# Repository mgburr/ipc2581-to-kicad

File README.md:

# IPC-2581 / ODB++ to KiCad Converter

A command-line utility and GUI application that converts IPC-2581 XML and ODB++ files to KiCad `.kicad_pcb` format.

## Features

- Converts **IPC-2581** revision B/C XML files to KiCad PCB format
- Converts **ODB++** archives (.tgz, .zip) and extracted directories to KiCad PCB format
- Supports **KiCad 7.x**, **8.x**, and **9.x** output formats
- Parses complete PCB data:
  - Board outline (with arcs/curves)
  - Layer stackup with materials and dielectric properties
  - Component footprints and placements
  - Copper traces and arcs
  - Vias (through-hole and blind/buried)
  - Copper pours/zones
  - Pad stacks (SMD, through-hole, NPTH)
  - Net connectivity
  - Silkscreen, soldermask, paste layers
- JSON import/export for interoperability
- GUI application for easy point-and-click conversion
- Cross-platform (macOS, Linux, Windows)

## Building

### Requirements

- CMake 3.14+
- C++17 compiler (GCC, Clang, MSVC)
- Python 3.x (required for ODB++ support and GUI)

### Build Steps

```bash
mkdir build && cd build
cmake ..
make
```

The executable `ipc2581-to-kicad` will be created in the `build/` directory.

## Usage

### Command Line

```
Usage: ipc2581-to-kicad [options] <input>

Supported input formats:
  .xml, .cvg          IPC-2581 XML files
  .tgz, .tar.gz, .zip ODB++ archives (requires Python 3)
  directory/           ODB++ extracted directory (requires Python 3)
  .json                JSON (with --import-json)

Options:
  -o, --output <file>       Output .kicad_pcb file (default: <input>.kicad_pcb)
  -v, --version <7|8|9>     Target KiCad version (default: 9)
  -s, --step <name>         Step name to convert (default: first step)
  --list-steps              List available steps and exit
  --list-layers             List layer mapping and exit
  --export-json             Export parsed PCB data as JSON to stdout
  --import-json             Import from JSON file (output of --export-json)
  --verbose                 Verbose output during conversion
  -h, --help                Show help
```

### Examples

```bash
# Convert IPC-2581 XML (auto-detected by .xml extension)
./build/ipc2581-to-kicad board.xml

# Convert ODB++ archive (auto-detected by .tgz extension)
./build/ipc2581-to-kicad board.tgz -o output.kicad_pcb

# Convert ODB++ directory
./build/ipc2581-to-kicad /path/to/odb_directory/ -o output.kicad_pcb

# Specify KiCad version
./build/ipc2581-to-kicad -v 8 board.tgz -o output.kicad_pcb

# List available steps
./build/ipc2581-to-kicad --list-steps board.tgz

# Convert a specific step with verbose output
./build/ipc2581-to-kicad -s "MainBoard" --verbose board.xml

# Export to JSON, then re-import
./build/ipc2581-to-kicad --export-json board.xml > board.json
./build/ipc2581-to-kicad --import-json board.json -o board.kicad_pcb

# Show layer mapping
./build/ipc2581-to-kicad --list-layers board.xml
```

### ODB++ Python Parser (standalone)

The ODB++ parser can also be used directly:

```bash
# Output JSON to stdout
python3 odb/odb_to_json.py board.tgz

# List steps in an ODB++ archive
python3 odb/odb_to_json.py --list-steps board.tgz

# Verbose mode
python3 odb/odb_to_json.py -v board.tgz > board.json
```

### GUI Application

A graphical interface is available in the `gui/` folder:

```bash
# macOS/Linux
./gui/run_gui.sh

# Windows
gui\run_gui.bat

# macOS (double-click)
# Open gui/IPC2581-Converter.command in Finder
```

The GUI provides:
- File browser supporting both IPC-2581 (.xml, .cvg) and ODB++ (.tgz, .zip) files
- KiCad version selection (7, 8, or 9)
- Step selection dropdown
- Layer mapping preview
- 2D and 3D board viewers
- Progress indication and log output

## Architecture

```
IPC-2581 (.xml/.cvg)
  -> [C++: ipc2581_parser.cpp]
  -> PcbModel
  -> [C++: kicad_writer.cpp]
  -> .kicad_pcb

ODB++ (.tgz/.zip/dir)
  -> [Python: odb/odb_to_json.py]
  -> JSON (stdout)
  -> [C++: json_import.cpp]
  -> PcbModel
  -> [C++: kicad_writer.cpp]
  -> .kicad_pcb
```

Both paths share the same C++ `PcbModel` and `KicadWriter`, ensuring consistent output.

## Sample Files

A sample IPC-2581 file is provided in `samples/`:

```bash
./build/ipc2581-to-kicad samples/led_power_board.xml -o samples/led_power_board.kicad_pcb
```

Open the output in KiCad to see:
- 40x25mm board with rounded corner
- Voltage regulator circuit with LED
- SMD and through-hole components
- Top and bottom copper layers
- Ground plane (zone fill)
- Multiple net classes

## Layer Mapping

### IPC-2581

| IPC-2581 layerFunction | KiCad Layer |
|------------------------|-------------|
| SIGNAL, POWER_GROUND (top) | F.Cu |
| SIGNAL, POWER_GROUND (bottom) | B.Cu |
| SIGNAL, POWER_GROUND (inner) | In{N}.Cu |
| SOLDERMASK (top/bottom) | F.Mask / B.Mask |
| PASTEMASK (top/bottom) | F.Paste / B.Paste |
| SILKSCREEN (top/bottom) | F.SilkS / B.SilkS |
| ASSEMBLY (top/bottom) | F.Fab / B.Fab |
| BOARD_OUTLINE | Edge.Cuts |
| DOCUMENT | Cmts.User |

### ODB++

| ODB++ Layer Type | KiCad Layer |
|------------------|-------------|
| SIGNAL (first copper) | F.Cu |
| SIGNAL (last copper) | B.Cu |
| SIGNAL (inner copper) | In{N}.Cu |
| SOLDER_MASK | F.Mask / B.Mask |
| SILK_SCREEN | F.SilkS / B.SilkS |
| SOLDER_PASTE | F.Paste / B.Paste |
| COMPONENT | F.Fab / B.Fab |
| DRILL | (vias/holes) |

## Project Structure

```
ipc2581-to-kicad/
├── CMakeLists.txt          # Build configuration
├── README.md
├── src/
│   ├── main.cpp            # CLI entry point (IPC-2581 + ODB++ + JSON)
│   ├── pcb_model.h         # Intermediate data model
│   ├── geometry.h/.cpp     # Geometry primitives
│   ├── utils.h/.cpp        # Utility functions
│   ├── ipc2581_parser.h/.cpp  # IPC-2581 XML parser
│   ├── json_export.h/.cpp  # PcbModel -> JSON serialization
│   ├── json_import.h/.cpp  # JSON -> PcbModel deserialization
│   └── kicad_writer.h/.cpp # KiCad output writer
├── odb/
│   ├── __init__.py         # Python package
│   ├── pcb_model.py        # Python PCB data model
│   ├── odb_parser.py       # ODB++ format parser
│   ├── utils.py            # Utility functions
│   └── odb_to_json.py      # ODB++ -> JSON bridge
├── third_party/
│   ├── pugixml/            # XML parser (vendored)
│   └── nlohmann/           # JSON parser (vendored, single-header)
├── gui/
│   ├── ipc2581_gui.py      # Python/tkinter GUI
│   ├── pcb_data.py         # PCB data layer (supports IPC-2581 + ODB++)
│   ├── run_gui.sh          # Linux/macOS launcher
│   ├── run_gui.bat         # Windows launcher
│   └── IPC2581-Converter.command  # macOS double-click launcher
├── test/
│   └── test_odb.py         # ODB++ parser and JSON bridge tests
└── samples/
    └── led_power_board.xml # Sample IPC-2581 file
```

## Testing

```bash
# Run ODB++ unit tests
python3 -m pytest test/test_odb.py -v
```

## Technical Notes

### Coordinate System
Both IPC-2581 and ODB++ use Y+ up, while KiCad uses Y+ down. The converter automatically flips Y coordinates.

### Arc Conversion
IPC-2581 uses center+sweep angle arcs; ODB++ uses center+CW/CCW arcs; KiCad uses start/mid/end points. Both parsers handle these transformations.

### UUID Generation
KiCad 8/9 requires UUIDs on all elements. The converter generates deterministic UUIDs based on object properties to ensure reproducible output.

### JSON Schema
The JSON interchange format is documented in the source. Use `--export-json` to see the schema for any input file. The same schema is produced by both the C++ IPC-2581 parser and the Python ODB++ parser.

## License

MIT License

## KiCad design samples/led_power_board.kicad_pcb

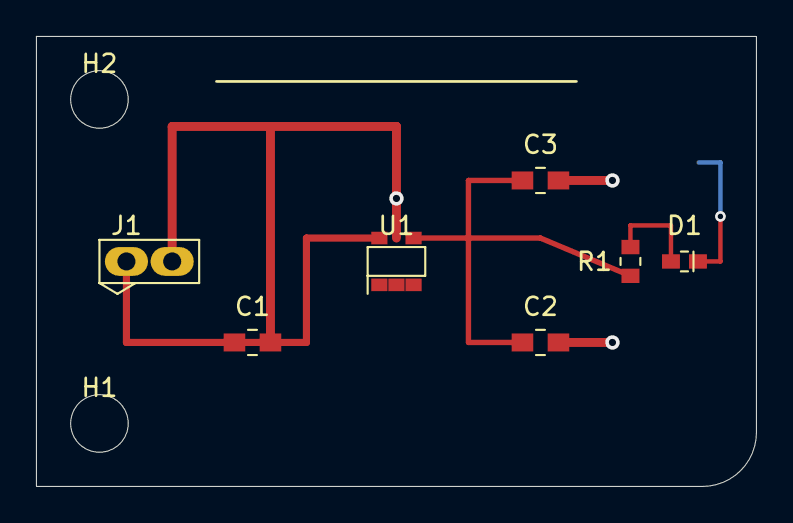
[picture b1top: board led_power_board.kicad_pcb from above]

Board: 2 copper layers, 40.0 x 25.0 mm, 10 parts (1 on the bottom side), 5 nets.

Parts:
C1, C2: 10uF; C_0805
C3: 100nF; C_0805
D1: GREEN; LED_0603
H1, H2: MountingHole_3.2mm
J1: Power; CONN_1x02_P2.54
R1: 330R; R_0603
R2: 10K; R_0603
U1: AP2112K-3.3; SOT-23-5

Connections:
GND: C1.2, C2.2, C3.2, J1.2, R2.2, U1.2
LED_A: D1.1, R1.2
LED_K: D1.2, R2.1
VIN: C1.1, J1.1, U1.1
VOUT: C2.1, C3.1, R1.1, U1.3
